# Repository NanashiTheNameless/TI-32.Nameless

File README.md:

# TI-32

## NamelessNanashi version with erroring towards my personal preferences, no warranty of any kind, not yet tested, DO NOT EXPECT TO WORK PERFECTLY YET

## Documentation

Read the DOCUMENTATION.md file

## Video

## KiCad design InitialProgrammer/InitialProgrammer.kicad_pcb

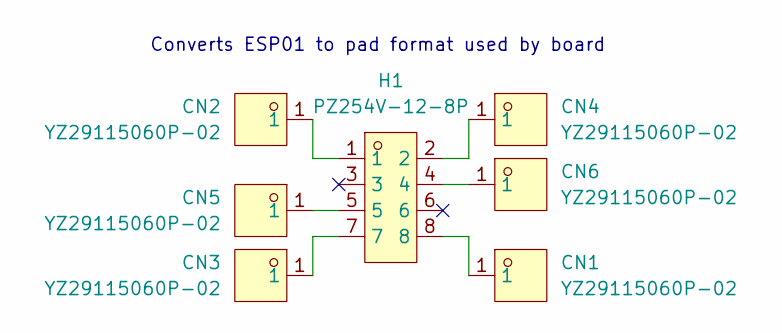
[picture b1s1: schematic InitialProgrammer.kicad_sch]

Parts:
CN1, CN2, CN3, CN4, CN5, CN6: YZ29115060P-02; TESTPOINT-SMD_BD2.0-D0.7; LCSC Part C5157350
H1: PZ254V-12-8P; HDR-TH_8P-P2.54-V-M-R2-C4-S2.54; LCSC Part C492421

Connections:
unnamed: CN1.1, H1.8
unnamed: CN2.1, H1.1
unnamed: CN3.1, H1.7
unnamed: CN4.1, H1.2
unnamed: CN5.1, H1.5
unnamed: CN6.1, H1.4

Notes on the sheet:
Converts ESP01 to pad format used by board

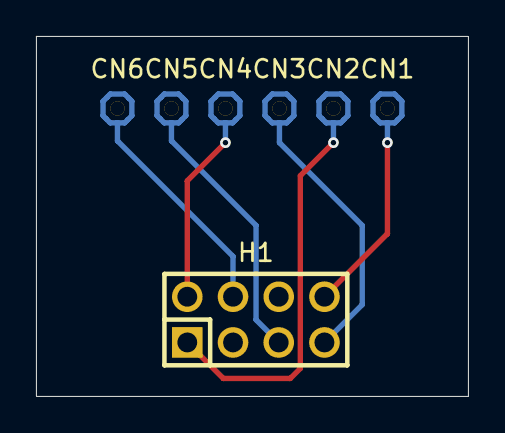
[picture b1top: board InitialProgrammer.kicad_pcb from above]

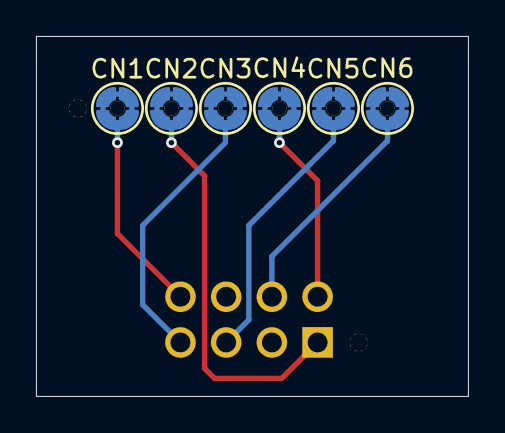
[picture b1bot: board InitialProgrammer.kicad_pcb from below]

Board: 2 copper layers, 24.0 x 20.0 mm, 7 parts (6 on the bottom side), 6 nets.

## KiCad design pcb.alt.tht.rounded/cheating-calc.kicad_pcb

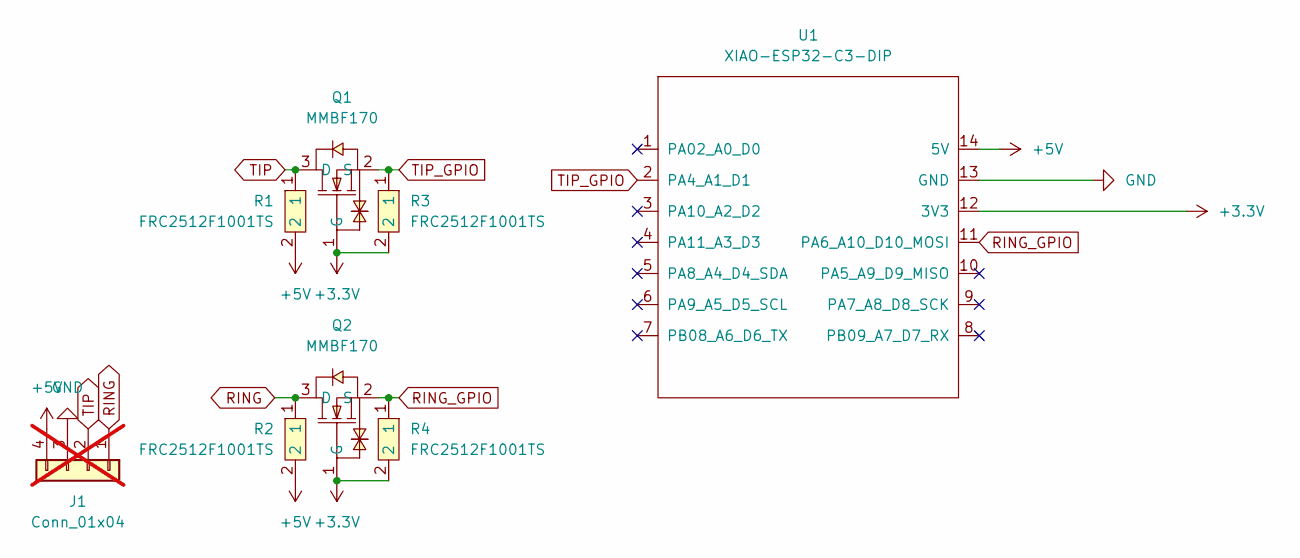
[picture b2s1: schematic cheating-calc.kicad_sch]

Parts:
J1: Conn_01x04; PinHeader_1x04_P2.54mm_Vertical; not fitted
Q1, Q2: MMBF170; SOT-23-3_L2.9-W1.6-P1.90-LS2.8-BR; LCSC Part C130879
R1, R2, R3, R4: FRC2512F1001TS; R2512; LCSC Part C2960683
U1: XIAO-ESP32-C3-DIP

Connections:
+3.3V: Q1.1 (G), Q2.1 (G), R3.2, R4.2, U1.12 (3V3)
+5V: J1.4, R1.2, R2.2, U1.14 (5V)
GND: J1.3, U1.13 (GND)
RING: J1.1, Q2.3 (D), R2.1
RING_GPIO: Q2.2 (S), R4.1, U1.11 (PA6_A10_D10_MOSI)
TIP: J1.2, Q1.3 (D), R1.1
TIP_GPIO: Q1.2 (S), R3.1, U1.2 (PA4_A1_D1)

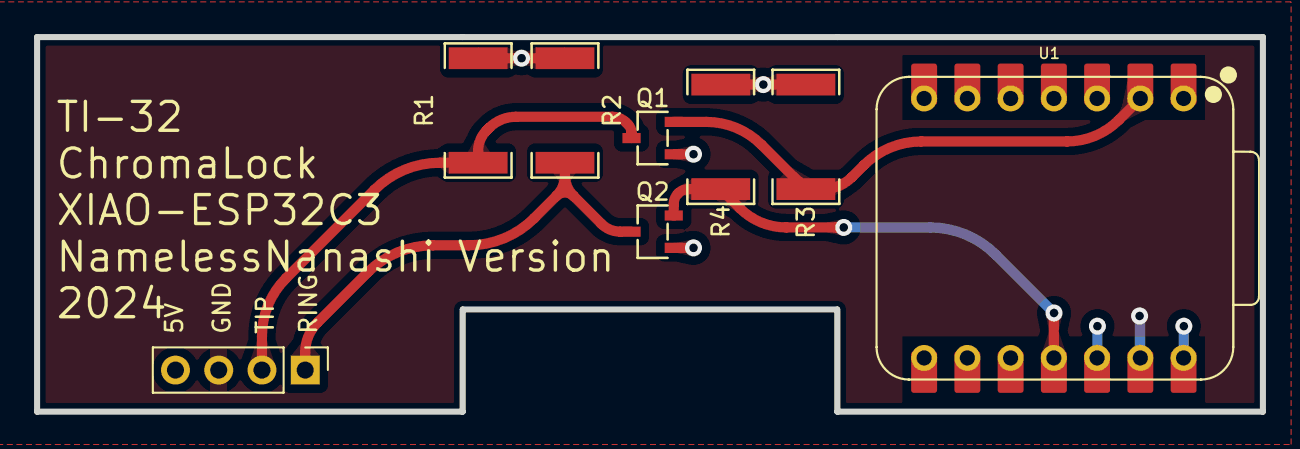
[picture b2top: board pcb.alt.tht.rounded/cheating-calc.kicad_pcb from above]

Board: 2 copper layers, 72.0 x 22.0 mm, 8 parts (0 on the bottom side), 7 nets.

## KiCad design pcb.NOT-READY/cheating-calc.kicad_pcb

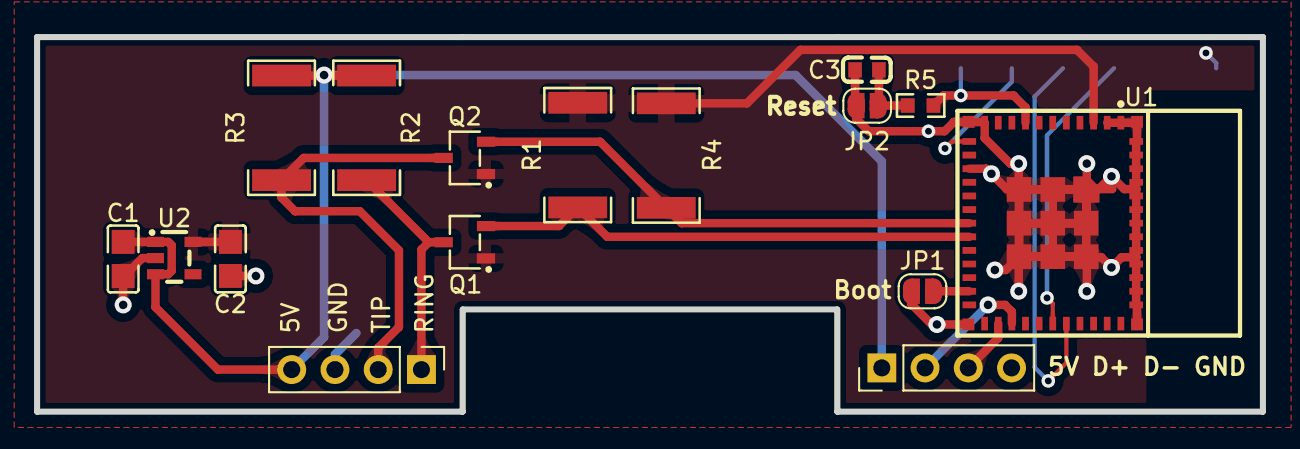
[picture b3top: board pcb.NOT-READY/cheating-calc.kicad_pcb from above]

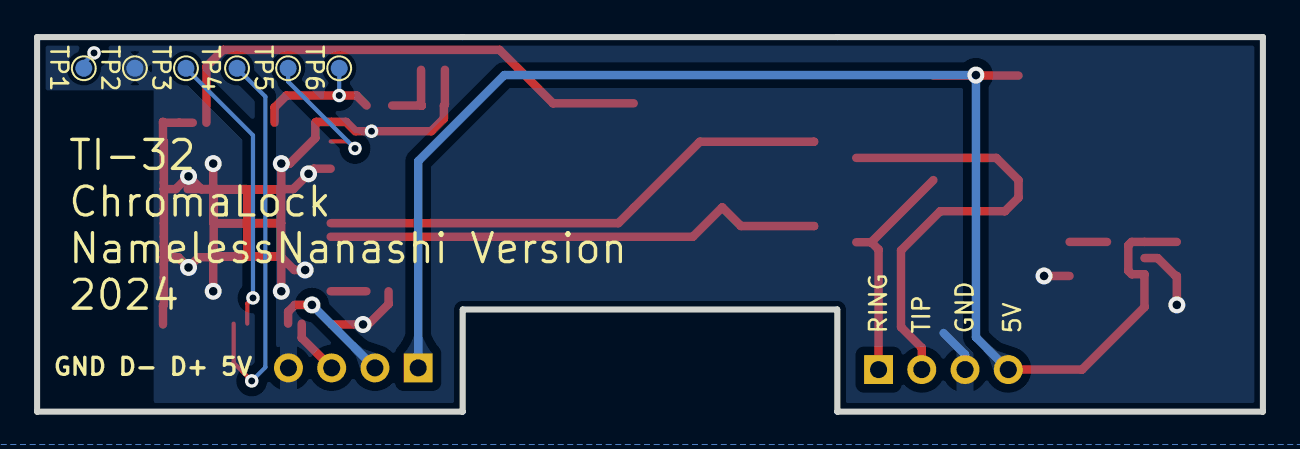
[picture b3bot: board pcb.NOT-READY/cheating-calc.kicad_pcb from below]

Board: 2 copper layers, 72.0 x 22.0 mm, 22 parts (6 on the bottom side), 15 nets.

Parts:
C1, C2: CL21B105KPFNNNE; C0805
C3: CC0603KRX7R9BB104; C0603
J1, J2: Conn_01x04; PinHeader_1x04_P2.54mm_Vertical
JP1, JP2: SolderJumper_2_Open; SolderJumper-2_P1.3mm_Open_RoundedPad1.0x1.5mm
Q1, Q2: MMBF170; SOT-23-3_L2.9-W1.6-P1.90-LS2.8-BR
R1, R2, R3, R4: FRC2512F1001TS; R2512
R5: 0603WAF1002T5E; R0603
TP1, TP2, TP3, TP4, TP5, TP6: TestPoint; TestPoint_Pad_D1.0mm
U1: ESP32-C3-MINI-1-N4; WIFIM-SMD_ESP32-C3-MINI-1
U2: TPLP5907MFX-3.3; SOT-23-5_L2.9-W1.6-P0.95-LS2.8-BR

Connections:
+3.3V: C2.1, Q1.1 (G), Q2.1 (G), R1.2, R4.2, TP1.1, U1.3 (3V3), U2.5 (VOUT)
+5V: C1.1, J1.4, J2.1, R2.2, R3.2, U2.1 (VIN), U2.3 (EN)
/D+: J2.2, U1.27 (IO19)
/D-: J2.3, U1.26 (IO18)
GND: C1.2, C2.2, C3.1, J1.3, J2.4, JP1.1 (A), JP2.1 (A), TP2.1, U1.1 (GND), U1.2 (GND), U1.11 (GND), U1.14 (GND), U1.36 (GND), U1.37 (GND), U1.38 (GND), U1.39 (GND), U1.40 (GND), U1.41 (GND), U1.42 (GND), U1.43 (GND), U1.44 (GND), U1.45 (GND), U1.46 (GND), U1.47 (GND), U1.48 (GND), U1.49 (GND), U1.50 (GND), U1.51 (GND), U1.52 (GND), U1.53 (GND), U2.2 (GND)
unnamed: JP1.2 (B), U1.23 (IO9)
unnamed: C3.2, JP2.2 (B), R5.1
unnamed: R5.2, TP6.1, U1.8 (EN)
unnamed: TP5.1, U1.12 (IO0)
unnamed: TP3.1, U1.30 (RXD0)
unnamed: TP4.1, U1.31 (TXD0)
RING: J1.1, Q1.3 (D), R2.1
RING_GPIO: Q1.2 (S), R1.1, U1.19 (IO5)
TIP: J1.2, Q2.3 (D), R3.1
TIP_GPIO: Q2.2 (S), R4.1, U1.18 (IO4)

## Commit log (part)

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2024-09-17 add all of my personal changes from my local machine
2024-09-17 point it to the raw blob link because linking through submodules apparently does not work
2024-10-19 update from upstream
2024-10-19 add missing datasheet to module
2024-10-20 add rounded version of my NOT-READY PCB
2024-11-13 update to be more upstream compatibl
2024-11-13 update typo
2024-11-13 lint documentation.md
2024-11-13 update cap
2024-12-10 update upstream
2025-07-16 Bump the npm_and_yarn group across 1 directory with 3 updates
    Bumps the npm_and_yarn group with 3 updates in the /server directory: [axios](https://github.com/axios/axios), [path-to-regexp](https://github.com/pillarjs/path-to-regexp) and [express](https://githu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
    Updates `axios` from 1.7.7 to 1.8.2
    - [Release notes](https://github.com/axios/axios/releases)
    - [Changelog](https://github.com/axios/axios/blob/v1.x/CHANGELOG.md)
    - [Commits](https://github.com/axios/axios/compare/v1.7.7...v1.8.2)
    Updates `path-to-regexp` from 0.1.10 to 0.1.12
2025-07-16 Bump express from 4.21.2 to 5.1.0 in /server
    ---
    updated-dependencies:
    - dependency-name: express
    dependency-version: 5.1.0
    dependency-type: direct:production
    update-type: version-update:semver-major
2025-07-16 Potential fix for code scanning alert no. 1: Loop bound injection
2025-07-16 Potential fix for code scanning alert no. 4: Stored cross-site scripting
2025-07-16 Potential fix for code scanning alert no. 17: Stored cross-site scripting
2025-07-28 Bump openai from 5.10.1 to 5.10.2 in /server
    Bumps [openai](https://github.com/openai/openai-node) from 5.10.1 to 5.10.2.
    - [Release notes](https://github.com/openai/openai-node/releases)
    - [Changelog](https://github.com/openai/openai-node/blob/master/CHANGELOG.md)
    - [Commits](https://github.com/openai/openai-node/compare/v5.10.1...v5.10.2)
    ---
    updated-dependencies:
2025-08-03 Bump morgan from 1.10.0 to 1.10.1 in /server
    Bumps [morgan](https://github.com/expressjs/morgan) from 1.10.0 to 1.10.1.
    - [Release notes](https://github.com/expressjs/morgan/releases)
    - [Changelog](https://github.com/expressjs/morgan/blob/master/HISTORY.md)
    - [Commits](https://github.com/expressjs/morgan/compare/1.10.0...1.10.1)
    ---
    updated-dependencies:
2025-08-11 Bump openai from 5.11.0 to 5.12.2 in /server
    Bumps [openai](https://github.com/openai/openai-node) from 5.11.0 to 5.12.2.
    - [Release notes](https://github.com/openai/openai-node/releases)
    - [Changelog](https://github.com/openai/openai-node/blob/master/CHANGELOG.md)
    - [Commits](https://github.com/openai/openai-node/compare/v5.11.0...v5.12.2)
    ---
    updated-dependencies:
2025-09-08 Bump dotenv from 17.2.1 to 17.2.2 in /server
    Bumps [dotenv](https://github.com/motdotla/dotenv) from 17.2.1 to 17.2.2.
    - [Changelog](https://github.com/motdotla/dotenv/blob/master/CHANGELOG.md)
    - [Commits](https://github.com/motdotla/dotenv/compare/v17.2.1...v17.2.2)
    ---
    updated-dependencies:
    - dependency-name: dotenv
2025-09-13 Bump axios in /server in the npm_and_yarn group across 1 directory
    Bumps the npm_and_yarn group with 1 update in the /server directory: [axios](https://github.com/axios/axios).
    Updates `axios` from 1.11.0 to 1.12.0
    - [Release notes](https://github.com/axios/axios/releases)
    - [Changelog](https://github.com/axios/axios/blob/v1.x/CHANGELOG.md)
    - [Commits](https://github.com/axios/axios/compare/v1.11.0...v1.12.0)
    ---
2025-09-15 Bump axios from 1.12.0 to 1.12.2 in /server
    Bumps [axios](https://github.com/axios/axios) from 1.12.0 to 1.12.2.
    - [Release notes](https://github.com/axios/axios/releases)
    - [Changelog](https://github.com/axios/axios/blob/v1.x/CHANGELOG.md)
    - [Commits](https://github.com/axios/axios/compare/v1.12.0...v1.12.2)
    ---
    updated-dependencies:
2025-10-06 Bump openai from 5.23.1 to 6.1.0 in /server
    Bumps [openai](https://github.com/openai/openai-node) from 5.23.1 to 6.1.0.
    - [Release notes](https://github.com/openai/openai-node/releases)
    - [Changelog](https://github.com/openai/openai-node/blob/master/CHANGELOG.md)
    - [Commits](https://github.com/openai/openai-node/compare/v5.23.1...v6.1.0)
    ---
    updated-dependencies:
2025-10-13 Bump openai from 6.1.0 to 6.3.0 in /server
    Bumps [openai](https://github.com/openai/openai-node) from 6.1.0 to 6.3.0.
    - [Release notes](https://github.com/openai/openai-node/releases)
    - [Changelog](https://github.com/openai/openai-node/blob/master/CHANGELOG.md)
    - [Commits](https://github.com/openai/openai-node/compare/v6.1.0...v6.3.0)
    ---
    updated-dependencies:
2025-11-03 Bump axios from 1.12.2 to 1.13.1 in /server
    Bumps [axios](https://github.com/axios/axios) from 1.12.2 to 1.13.1.
    - [Release notes](https://github.com/axios/axios/releases)
    - [Changelog](https://github.com/axios/axios/blob/v1.x/CHANGELOG.md)
    - [Commits](https://github.com/axios/axios/compare/v1.12.2...v1.13.1)
    ---
    updated-dependencies:
2025-11-10 Bump axios from 1.13.1 to 1.13.2 in /server
    Bumps [axios](https://github.com/axios/axios) from 1.13.1 to 1.13.2.
    - [Release notes](https://github.com/axios/axios/releases)
    - [Changelog](https://github.com/axios/axios/blob/v1.x/CHANGELOG.md)
    - [Commits](https://github.com/axios/axios/compare/v1.13.1...v1.13.2)
    ---
    updated-dependencies:
2025-11-24 Bump openai from 6.9.0 to 6.9.1 in /server
    Bumps [openai](https://github.com/openai/openai-node) from 6.9.0 to 6.9.1.
    - [Release notes](https://github.com/openai/openai-node/releases)
    - [Changelog](https://github.com/openai/openai-node/blob/master/CHANGELOG.md)
    - [Commits](https://github.com/openai/openai-node/compare/v6.9.0...v6.9.1)
    ---
    updated-dependencies:
2025-12-08 Bump openai from 6.9.1 to 6.10.0 in /server
    Bumps [openai](https://github.com/openai/openai-node) from 6.9.1 to 6.10.0.
    - [Release notes](https://github.com/openai/openai-node/releases)
    - [Changelog](https://github.com/openai/openai-node/blob/master/CHANGELOG.md)
    - [Commits](https://github.com/openai/openai-node/compare/v6.9.1...v6.10.0)
    ---
    updated-dependencies:
2026-01-01 Bump qs in /server in the npm_and_yarn group across 1 directory
    Bumps the npm_and_yarn group with 1 update in the /server directory: [qs](https://github.com/ljharb/qs).
    Updates `qs` from 6.14.0 to 6.14.1
    - [Changelog](https://github.com/ljharb/qs/blob/main/CHANGELOG.md)
    - [Commits](https://github.com/ljharb/qs/compare/v6.14.0...v6.14.1)
    ---
    updated-dependencies:
2026-01-23 Bump lodash in /server in the npm_and_yarn group across 1 directory
    Bumps the npm_and_yarn group with 1 update in the /server directory: [lodash](https://github.com/lodash/lodash).
    Updates `lodash` from 4.17.21 to 4.17.23
    - [Release notes](https://github.com/lodash/lodash/releases)
    - [Commits](https://github.com/lodash/lodash/compare/4.17.21...4.17.23)
    ---
    updated-dependencies:
2026-02-02 Bump axios from 1.13.3 to 1.13.4 in /server
    Bumps [axios](https://github.com/axios/axios) from 1.13.3 to 1.13.4.
    - [Release notes](https://github.com/axios/axios/releases)
    - [Changelog](https://github.com/axios/axios/blob/v1.x/CHANGELOG.md)
    - [Commits](https://github.com/axios/axios/compare/v1.13.3...v1.13.4)
    ---
    updated-dependencies:
2026-02-09 Bump axios from 1.13.4 to 1.13.5 in /server
    Bumps [axios](https://github.com/axios/axios) from 1.13.4 to 1.13.5.
    - [Release notes](https://github.com/axios/axios/releases)
    - [Changelog](https://github.com/axios/axios/blob/v1.x/CHANGELOG.md)
    - [Commits](https://github.com/axios/axios/compare/v1.13.4...v1.13.5)
    ---
    updated-dependencies:
2026-02-14 Bump qs in /server in the npm_and_yarn group across 1 directory
    Bumps the npm_and_yarn group with 1 update in the /server directory: [qs](https://github.com/ljharb/qs).
    Updates `qs` from 6.14.1 to 6.14.2
    - [Changelog](https://github.com/ljharb/qs/blob/main/CHANGELOG.md)
    - [Commits](https://github.com/ljharb/qs/compare/v6.14.1...v6.14.2)
    ---
    updated-dependencies:
2026-02-16 Bump openai from 6.18.0 to 6.22.0 in /server
    Bumps [openai](https://github.com/openai/openai-node) from 6.18.0 to 6.22.0.
    - [Release notes](https://github.com/openai/openai-node/releases)
    - [Changelog](https://github.com/openai/openai-node/blob/master/CHANGELOG.md)
    - [Commits](https://github.com/openai/openai-node/compare/v6.18.0...v6.22.0)
    ---
    updated-dependencies:
2026-03-06 Bump express-rate-limit
    Bumps the npm_and_yarn group with 1 update in the /server directory: [express-rate-limit](https://github.com/express-rate-limit/express-rate-limit).
    Updates `express-rate-limit` from 8.2.1 to 8.2.2
    - [Release notes](https://github.com/express-rate-limit/express-rate-limit/releases)
    - [Commits](https://github.com/express-rate-limit/express-rate-limit/compare/v8.2.1...v8.2.2)
    ---
    updated-dependencies:
2026-03-16 Bump openai from 6.27.0 to 6.29.0 in /server
    Bumps [openai](https://github.com/openai/openai-node) from 6.27.0 to 6.29.0.
    - [Release notes](https://github.com/openai/openai-node/releases)
    - [Changelog](https://github.com/openai/openai-node/blob/master/CHANGELOG.md)
    - [Commits](https://github.com/openai/openai-node/compare/v6.27.0...v6.29.0)
    ---
    updated-dependencies:
2026-03-23 Bump openai from 6.29.0 to 6.32.0 in /server
    Bumps [openai](https://github.com/openai/openai-node) from 6.29.0 to 6.32.0.
    - [Release notes](https://github.com/openai/openai-node/releases)
    - [Changelog](https://github.com/openai/openai-node/blob/master/CHANGELOG.md)
    - [Commits](https://github.com/openai/openai-node/compare/v6.29.0...v6.32.0)
    ---
    updated-dependencies:
2026-03-30 Bump axios from 1.13.6 to 1.14.0 in /server
    Bumps [axios](https://github.com/axios/axios) from 1.13.6 to 1.14.0.
    - [Release notes](https://github.com/axios/axios/releases)
    - [Changelog](https://github.com/axios/axios/blob/v1.x/CHANGELOG.md)
    - [Commits](https://github.com/axios/axios/compare/v1.13.6...v1.14.0)
    ---
    updated-dependencies:
2026-04-06 Bump dotenv from 17.3.1 to 17.4.1 in /server
    Bumps [dotenv](https://github.com/motdotla/dotenv) from 17.3.1 to 17.4.1.
    - [Changelog](https://github.com/motdotla/dotenv/blob/master/CHANGELOG.md)
    - [Commits](https://github.com/motdotla/dotenv/compare/v17.3.1...v17.4.1)
    ---
    updated-dependencies:
    - dependency-name: dotenv
2026-04-13 Bump openai from 6.33.0 to 6.34.0 in /server
    Bumps [openai](https://github.com/openai/openai-node) from 6.33.0 to 6.34.0.
    - [Release notes](https://github.com/openai/openai-node/releases)
    - [Changelog](https://github.com/openai/openai-node/blob/master/CHANGELOG.md)
    - [Commits](https://github.com/openai/openai-node/compare/v6.33.0...v6.34.0)
    ---
    updated-dependencies:
2026-05-07 Bump ip-address in /server in the npm_and_yarn group across 1 directory
    Bumps the npm_and_yarn group with 1 update in the /server directory: [ip-address](https://github.com/beaugunderson/ip-address).
    Updates `ip-address` from 10.1.0 to 10.2.0
    - [Commits](https://github.com/beaugunderson/ip-address/commits)
    ---
    updated-dependencies:
    - dependency-name: ip-address
